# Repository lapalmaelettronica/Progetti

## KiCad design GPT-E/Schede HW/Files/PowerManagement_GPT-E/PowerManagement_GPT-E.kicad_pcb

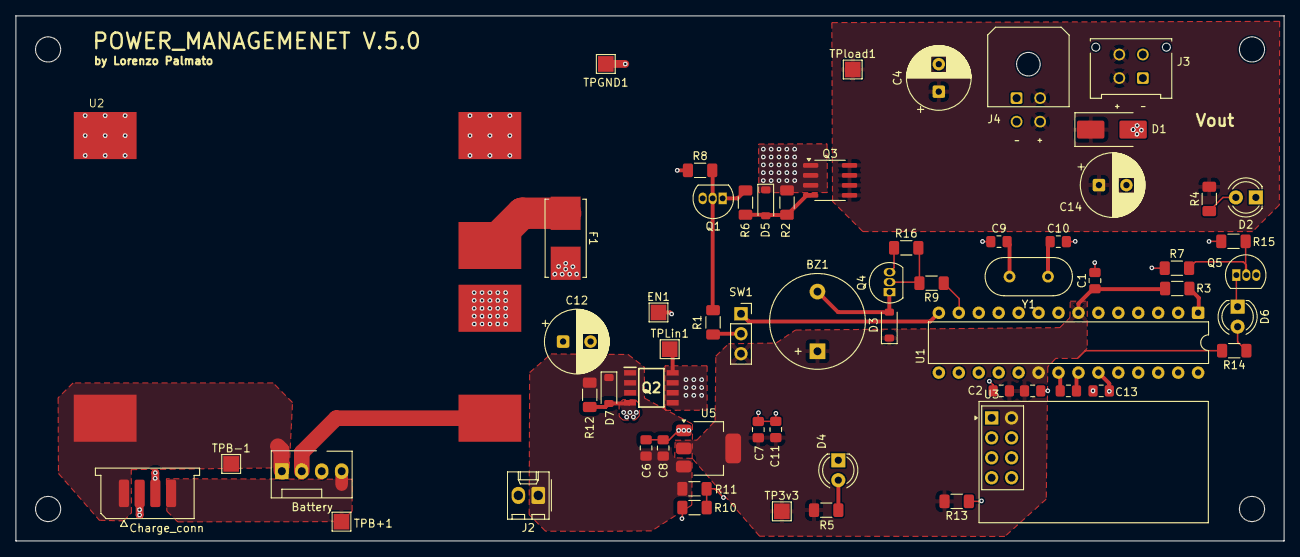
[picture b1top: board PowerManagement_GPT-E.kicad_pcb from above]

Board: 4 copper layers, 161.5 x 66.9 mm, 62 parts (0 on the bottom side), 36 nets.

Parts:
BZ1: TMB12A03; Buzzer_12x9.5RM7.6
C1, C3, C5, C8, C11, C13: 100n; C_0805_2012Metric_Pad1.18x1.45mm_HandSolder
C2, C6, C7: 10uF; C_0805_2012Metric_Pad1.18x1.45mm_HandSolder
C4, C12, C14: 470u; CP_Radial_D8.0mm_P3.50mm
C9, C10: 22p; C_0805_2012Metric_Pad1.18x1.45mm_HandSolder
D1: Z2SMBxxx; D_SMB_Handsoldering
D2: LED; LED_D4.0mm
D3: 1N4148W; D_SOD-123
D4: LED_LoadON; LED_D4.0mm
D5, D7: BZT52C12; D_SOD-123
D6: LED_SENSE; LED_D4.0mm
EN1: TestPoint; TestPoint_Pad_2.0x2.0mm
F1: Fuse_Small; Fuseholder_Littelfuse_Nano2_154x
J1: Battery; FanPinHeader_1x04_P2.54mm_Vertical
J2: switch; Molex_KK-254_AE-6410-02A_1x02_P2.54mm_Vertical
J3: Conn_02x02_Counter_Clockwise; Molex_Micro-Fit_3.0_43045-0412_2x02_P3.00mm_Vertical
J4: Conn_02x02_Counter_Clockwise; Molex_Micro-Fit_3.0_43045-0400_2x02_P3.00mm_Horizontal
J7: Charge_conn; Samtec_UMPS-04-XX.X-X-V-S_1x04_P2.0mm_Socket
Q1, Q4, Q5: BC547; TO-92L_Inline
Q2: IRF7416TRPBF; SOIC-8
Q3: AO4407; SOIC-8_3.9x4.9mm_P1.27mm
R1, R7, R9: 4.7k; R_1206_3216Metric_Pad1.30x1.75mm_HandSolder
R2, R8, R10, R12, R15, R16: 100K; R_1206_3216Metric_Pad1.30x1.75mm_HandSolder
R3, R13: 10k; R_1206_3216Metric_Pad1.30x1.75mm_HandSolder
R4: 2.2k; R_1206_3216Metric_Pad1.30x1.75mm_HandSolder
R5, R14: 330; R_1206_3216Metric_Pad1.30x1.75mm_HandSolder
R6: 100; R_1206_3216Metric_Pad1.30x1.75mm_HandSolder
R11: 33k; R_1206_3216Metric_Pad1.30x1.75mm_HandSolder
SW1: SW_SPDT; PinSocket_1x03_P2.54mm_Vertical
TP3v3: TestPoint; TestPoint_Pad_2.0x2.0mm
TPB+1: TestPoint; TestPoint_Pad_2.0x2.0mm
TPB-1: TestPoint; TestPoint_Pad_2.0x2.0mm
TPGND1: TestPoint; TestPoint_Pad_2.0x2.0mm
TPLin1: TestPoint; TestPoint_Pad_2.0x2.0mm
TPload1: TestPoint; TestPoint_Pad_2.0x2.0mm
U1: ATmega8-16P; DIP-28_W7.62mm
U2: BMS_3S_LithiumBattery18650; BMS-4S
U3: NRF24L01_Breakout; nRF24L01_Breakout
U5: AZ1117CH2-3.3; SOT-223-3_TabPin2
Y1: 8MHz; Crystal_HC18-U_Vertical

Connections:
1s: J1.2, J7.2, U2.2 (B2)
2s: J1.3, J7.3, U2.3 (B3)
+3v3: BZ1.1 (+), C1.1, C2.1, C5.1, C7.1, C11.1, D3.1 (K), R3.2, R5.2, R13.2, R14.2, SW1.3 (C), TP3v3.1, U1.7 (VCC), U1.20 (AVCC), U3.2 (VCC), U5.2 (OUT)
BAT+: J1.4, J7.4, TPB+1.1, U2.4 (B+)
BAT-: J1.1, J7.1, TPB-1.1, U2.1 (B1)
CE: U1.15 (PB1), U3.3 (CE)
CSN: R13.1, U1.16 (PB2), U3.4 (~CSN)
EN: EN1.1, SW1.1 (A), U1.14 (PB0)
LOAD: C4.1, C14.1, D1.1 (K), J3.2, J3.4, J4.2, J4.4, Q3.5 (D), Q3.6 (D), Q3.7 (D), Q3.8 (D), R4.2, TPload1.1
MISO: U1.18 (PB4), U3.7 (MISO)
MOSI: U1.17 (PB3), U3.6 (MOSI)
unnamed: BZ1.2 (-), D3.2 (A), Q4.1 (C)
unnamed: D2.2 (A), R4.1
unnamed: D4.2 (A), R5.1
unnamed: D5.2 (A), Q3.4 (G), R2.2, R6.2
unnamed: D6.2 (A), R14.1
unnamed: D6.1 (K), Q5.1 (C)
unnamed: C12.1, F1.2, J2.2
unnamed: Q1.2 (B), R1.2, R8.2
unnamed: Q1.1 (C), R6.1
unnamed: Q4.2 (B), R9.2, R16.2
unnamed: Q5.2 (B), R7.2, R15.2
unnamed: R1.1, SW1.2 (B)
unnamed: C3.1, U1.21 (AREF)
unnamed: C10.1, U1.9 (PB6/XTAL1), Y1.1
unnamed: C9.2, U1.10 (PB7/XTAL2), Y1.2
unnamed: R3.1, U1.1 (PC6/~RESET)
unnamed: U1.4 (PD2), U3.8 (IRQ)
unnamed: R7.1, U1.11 (PD5)
unnamed: R9.1, U1.13 (PD7)
unnamed: F1.1, U2.5 (P+)
P+: C6.1, C8.1, D7.1 (K), J2.1, Q2.1 (S_1), Q2.2 (S_2), Q2.3 (S_3), R10.2, R12.2, U5.3 (IN)
P-: C1.2, C2.2, C3.2, C4.2, C5.2, C6.2, C7.2, C8.2, C9.1, C10.2, C11.2, C12.2, C13.2, C14.2, D1.2 (A), D2.1 (K), D4.1 (K), D7.2 (A), J3.1, J3.3, J4.1, J4.3, Q1.3 (E), Q2.4 (G), Q4.3 (E), Q5.3 (E), R8.1, R11.1, R12.1, R15.1, R16.1, TPGND1.1, U1.8 (GND), U1.22 (AGND), U2.6 (P-), U3.1 (GND), U5.1 (GND)
SCK: U1.19 (PB5), U3.5 (SCK)
Vsense: C13.1, R10.1, R11.2, U1.23 (PC0)
toLOAD: D5.1 (K), Q2.5 (D_1), Q2.6 (D_2), Q2.7 (D_3), Q2.8 (D_4), Q3.1 (S), Q3.2 (S), Q3.3 (S), R2.1, TPLin1.1

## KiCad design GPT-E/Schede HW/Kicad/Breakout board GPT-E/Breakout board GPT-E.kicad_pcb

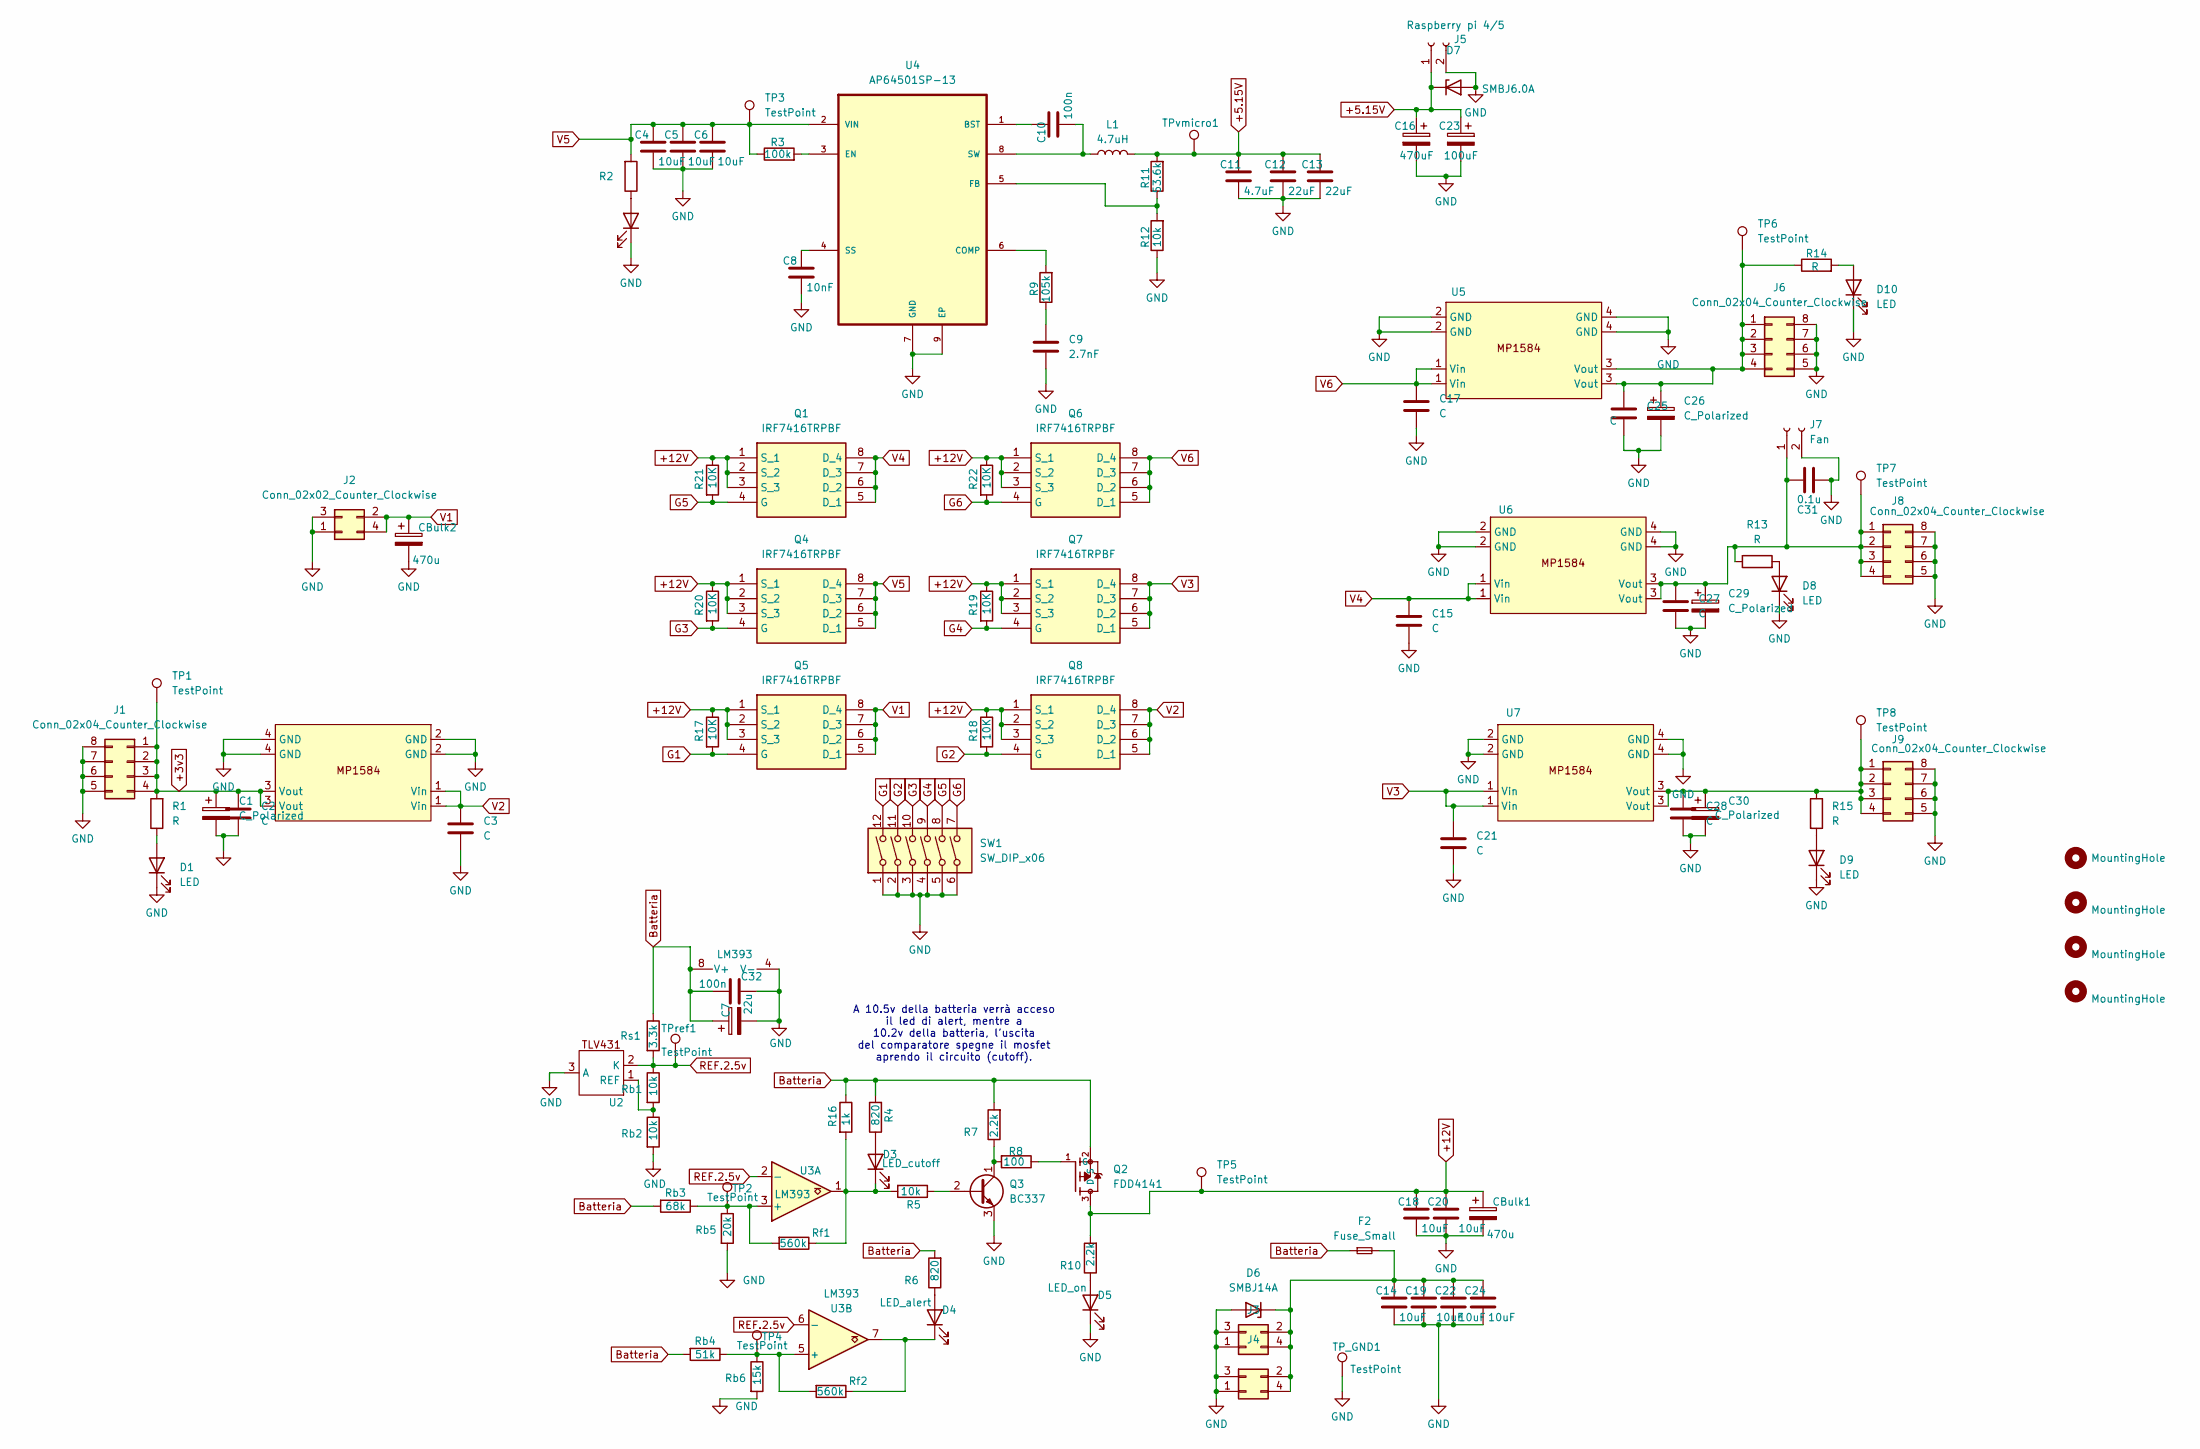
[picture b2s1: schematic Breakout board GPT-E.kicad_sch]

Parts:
C1, C26, C29, C30: C_Polarized; CP_Radial_D6.3mm_P2.50mm
C2, C3, C15, C17, C21, C25, C27, C28: C; C_Disc_D5.1mm_W3.2mm_P5.00mm
C4, C5, C6, C14, C18, C19, C20, C22, C24: 10uF; C_0805_2012Metric_Pad1.18x1.45mm_HandSolder
C7: 22u; CP_Radial_D4.0mm_P1.50mm
C8: 10nF; C_0805_2012Metric_Pad1.18x1.45mm_HandSolder
C9: 2.7nF; C_Disc_D5.0mm_W2.5mm_P2.50mm
C10, C32: 100n; C_0805_2012Metric_Pad1.18x1.45mm_HandSolder
C11: 4.7uF; C_0805_2012Metric_Pad1.18x1.45mm_HandSolder
C12, C13: 22uF; C_0805_2012Metric_Pad1.18x1.45mm_HandSolder
C16: 470uF; CP_Radial_D5.0mm_P2.00mm
C23: 100uF; CP_Radial_D5.0mm_P2.00mm
C31: 0.1u; C_Disc_D5.1mm_W3.2mm_P5.00mm
CBulk1, CBulk2: 470u; CP_Radial_D6.3mm_P2.50mm
D1, D2, D8, D9, D10: LED; LED_D4.0mm
D3: LED_cutoff; LED_D4.0mm
D4: LED_alert; LED_D4.0mm
D5: LED_on; LED_D4.0mm
D6: SMBJ14A; D_SMB_Handsoldering
D7: SMBJ6.0A; D_SMB_Handsoldering
F2: Fuse_Small; Fuseholder_Littelfuse_Nano2_154x
H1, H2, H3, H4: MountingHole; MountingHole_3.2mm_M3
J1, J6, J8, J9: Conn_02x04_Counter_Clockwise; Molex_Micro-Fit_3.0_43045-0812_2x04_P3.00mm_Vertical
J2, J4: Conn_02x02_Counter_Clockwise; Molex_Micro-Fit_3.0_43045-0412_2x02_P3.00mm_Vertical
J3: Conn_02x02_Counter_Clockwise; Molex_Micro-Fit_3.0_43045-0400_2x02_P3.00mm_Horizontal
J5: Raspberry pi 4/5; TerminalBlock_TE_282834-2_1x02_P2.54mm_Horizontal
J7: Fan; PinHeader_1x02_P2.54mm_Vertical
L1: 4.7uH; L_Changjiang_FXL0630
Q1, Q4, Q5, Q6, Q7, Q8: IRF7416TRPBF; SOIC-8; Mouser Part Number 942-IRF7416TRPBF
Q2: FDD4141; FDD4141-TO252
Q3: BC337; TO-92L_HandSolder
R1, R13, R14, R15: R; R_Axial_DIN0204_L3.6mm_D1.6mm_P5.08mm_Horizontal
R2: 470; R_1206_3216Metric_Pad1.30x1.75mm_HandSolder
R3: 100k; R_1206_3216Metric_Pad1.30x1.75mm_HandSolder
R4, R6: 820; R_1206_3216Metric_Pad1.30x1.75mm_HandSolder
R5, R12: 10k; R_1206_3216Metric_Pad1.30x1.75mm_HandSolder
R7: 2.2k; R_1206_3216Metric_Pad1.30x1.75mm_HandSolder
R8: 100; R_1206_3216Metric_Pad1.30x1.75mm_HandSolder
R9: 105k; R_1206_3216Metric_Pad1.30x1.75mm_HandSolder
R10: 2.2k; R_Axial_DIN0204_L3.6mm_D1.6mm_P5.08mm_Horizontal
R11: 53.6k; R_1206_3216Metric_Pad1.30x1.75mm_HandSolder
R16: 1k; R_1206_3216Metric_Pad1.30x1.75mm_HandSolder
R17, R18, R19, R20, R21, R22: 10K; R_1206_3216Metric_Pad1.30x1.75mm_HandSolder
Rb1, Rb2: 10k; R_1206_3216Metric_Pad1.30x1.75mm_HandSolder
Rb3: 68k; R_1206_3216Metric_Pad1.30x1.75mm_HandSolder
Rb4: 51k; R_1206_3216Metric_Pad1.30x1.75mm_HandSolder
Rb5: 20k; R_1206_3216Metric_Pad1.30x1.75mm_HandSolder
Rb6: 15k; R_1206_3216Metric_Pad1.30x1.75mm_HandSolder
Rf1, Rf2: 560k; R_1206_3216Metric_Pad1.30x1.75mm_HandSolder
Rs1: 3.3k; R_1206_3216Metric_Pad1.30x1.75mm_HandSolder
SW1: SW_DIP_x06; SW_DIP_SPSTx06_Slide_6.7x16.8mm_W7.62mm_P2.54mm_LowProfile
TP1, TP2, TP3, TP4, TP5, TP6, TP7, TP8: TestPoint; TestPoint_Pad_D1.5mm
TP_GND1: TestPoint; TestPoint_Pad_D1.5mm
TPref1: TestPoint; TestPoint_Pad_D1.5mm
TPvmicro1: TestPoint; TestPoint_Pad_D1.5mm
U1, U5, U6, U7: MP1584EN
U2: SOT-23-3
U3: LM393; DIP-8_W7.62mm
U4: AP64501SP-13

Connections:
+3v3: C1.1, C2.1, J1.1, J1.2, J1.3, J1.4, R1.2, TP1.1, U1.3 (Vout)
+5.15V: C11.1, C12.1, C13.1, C16.1, C23.1, D7.1 (K), J5.1, L1.2, R11.2, TPvmicro1.1
+12V: C18.1, C20.1, CBulk1.1, Q1.1 (S_1), Q1.2 (S_2), Q1.3 (S_3), Q2.3 (D), Q4.1 (S_1), Q4.2 (S_2), Q4.3 (S_3), Q5.1 (S_1), Q5.2 (S_2), Q5.3 (S_3), Q6.1 (S_1), Q6.2 (S_2), Q6.3 (S_3), Q7.1 (S_1), Q7.2 (S_2), Q7.3 (S_3), Q8.1 (S_1), Q8.2 (S_2), Q8.3 (S_3), R10.2, R17.1, R18.1, R19.1, R20.1, R21.1, R22.1, TP5.1
Batteria: C7.1, C32.1, F2.1, Q2.2 (S), R4.2, R6.2, R7.2, R16.1, Rb3.2, Rb4.2, Rs1.1, U3.8 (V+)
G1: Q5.4 (G), R17.2, SW1.12
G2: Q8.4 (G), R18.2, SW1.11
G3: Q4.4 (G), R20.2, SW1.10
G4: Q7.4 (G), R19.2, SW1.9
G5: Q1.4 (G), R21.2, SW1.8
G6: Q6.4 (G), R22.2, SW1.7
GND: C1.2, C2.2, C3.2, C4.2, C5.2, C6.2, C7.2, C8.2, C9.2, C11.2, C12.2, C13.2, C14.2, C15.2, C16.2, C17.2, C18.2, C19.2, C20.2, C21.2, C22.2, C23.2, C24.2, C25.2, C26.2, C27.2, C28.2, C29.2, C30.2, C31.2, C32.2, CBulk1.2, CBulk2.2, D1.1 (K), D2.1 (K), D5.1 (K), D6.2 (A), D7.2 (A), D8.1 (K), D9.1 (K), D10.1 (K), J1.5, J1.6, J1.7, J1.8, J2.1, J2.3, J3.1, J3.3, J4.1, J4.3, J5.2, J6.5, J6.6, J6.7, J6.8, J7.2, J8.5, J8.6, J8.7, J8.8, J9.5, J9.6, J9.7, J9.8, Q3.3 (E), R12.1, Rb2.2, Rb5.2, Rb6.2, SW1.1, SW1.2, SW1.3, SW1.4, SW1.5, SW1.6, TP_GND1.1, U1.2 (GND), U1.4 (GND), U2.3 (A), U3.4 (V-), U4.7 (GND), U4.9 (EP), U5.2 (GND), U5.4 (GND), U6.2 (GND), U6.4 (GND), U7.2 (GND), U7.4 (GND)
unnamed: C9.1, R9.1
unnamed: D1.2 (A), R1.1
unnamed: D2.2 (A), R2.1
unnamed: D3.2 (A), R4.1
unnamed: D3.1 (K), R5.2, R16.2, Rf1.1, U3.1
unnamed: D4.2 (A), R6.1
unnamed: D4.1 (K), Rf2.1, U3.7
unnamed: D5.2 (A), R10.1
unnamed: C14.1, C19.1, C22.1, C24.1, D6.1 (K), F2.2, J3.2, J3.4, J4.2, J4.4
unnamed: D8.2 (A), R13.2
unnamed: D9.2 (A), R15.2
unnamed: D10.2 (A), R14.2
unnamed: C25.1, C26.1, J6.1, J6.2, J6.3, J6.4, R14.1, TP6.1, U5.3 (Vout)
unnamed: C27.1, C29.1, C31.1, J7.1, J8.1, J8.2, J8.3, J8.4, R13.1, TP7.1, U6.3 (Vout)
unnamed: C28.1, C30.1, J9.1, J9.2, J9.3, J9.4, R15.1, TP8.1, U7.3 (Vout)
unnamed: Q2.1 (G), R8.1
unnamed: Q3.2 (B), R5.1
unnamed: Q3.1 (C), R7.1, R8.2
unnamed: Rb1.2, Rb2.1, U2.1 (REF)
unnamed: Rb3.1, Rb5.1, Rf1.2, TP2.1, U3.3 (+)
unnamed: Rb4.1, Rb6.1, Rf2.2, TP4.1, U3.5 (+)
unnamed: C10.1, U4.1 (BST)
unnamed: R9.2, U4.6 (COMP)
unnamed: R3.2, U4.3 (EN)
unnamed: R11.1, R12.2, U4.5 (FB)
unnamed: C8.1, U4.4 (SS)
unnamed: C10.2, L1.1, U4.8 (SW)
REF.2.5v: Rb1.1, Rs1.2, TPref1.1, U2.2 (K), U3.2 (-), U3.6 (-)
V1: CBulk2.1, J2.2, J2.4, Q5.5 (D_1), Q5.6 (D_2), Q5.7 (D_3), Q5.8 (D_4)
V2: C3.1, Q8.5 (D_1), Q8.6 (D_2), Q8.7 (D_3), Q8.8 (D_4), U1.1 (Vin)
V3: C21.1, Q7.5 (D_1), Q7.6 (D_2), Q7.7 (D_3), Q7.8 (D_4), U7.1 (Vin)
V4: C15.1, Q1.5 (D_1), Q1.6 (D_2), Q1.7 (D_3), Q1.8 (D_4), U6.1 (Vin)
V5: C4.1, C5.1, C6.1, Q4.5 (D_1), Q4.6 (D_2), Q4.7 (D_3), Q4.8 (D_4), R2.2, R3.1, TP3.1, U4.2 (VIN)
V6: C17.1, Q6.5 (D_1), Q6.6 (D_2), Q6.7 (D_3), Q6.8 (D_4), U5.1 (Vin)

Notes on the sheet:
A 10.5v della batteria verrà acceso il led di alert, mentre a 10.2v della batteria, l'uscita del comparatore spegne il mosfet aprendo il circuito (cutoff).

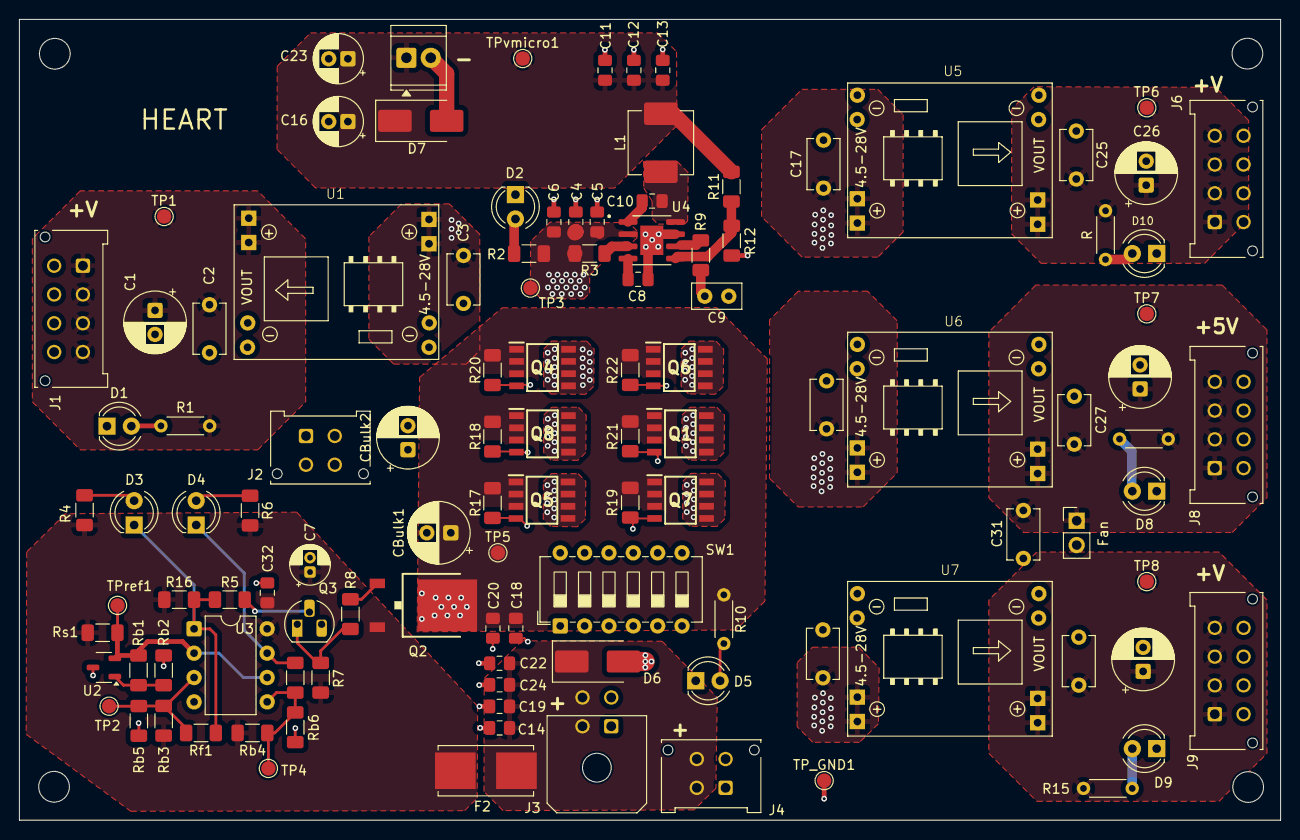
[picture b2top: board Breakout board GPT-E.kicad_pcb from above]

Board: 4 copper layers, 131.5 x 83.5 mm, 117 parts (0 on the bottom side), 45 nets.
